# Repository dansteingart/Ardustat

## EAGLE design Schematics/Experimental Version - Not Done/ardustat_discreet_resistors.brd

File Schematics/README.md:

## What's in this folder:

### Working Version
This works

### Experimental Versions
Largely Don't work and are poorly documented.

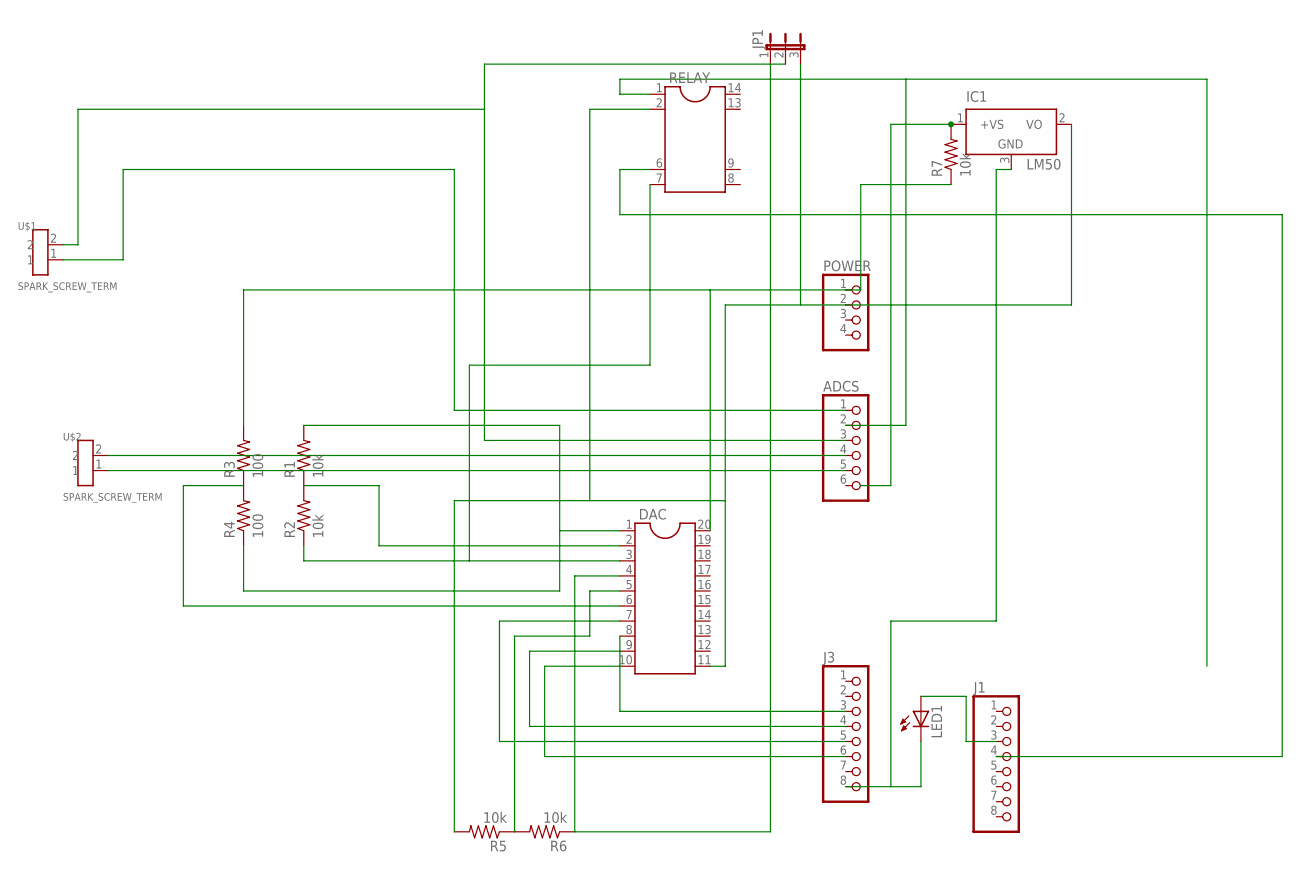
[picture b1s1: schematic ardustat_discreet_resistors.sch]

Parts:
ADCS: PINHD-1X6; 1X06
DAC: DIL20S; SOCKED-20
IC1: LM50; SOT23
J1, J3: PINHD-1X8; 1X08
JP1: JP2E; JP2
LED1: LED5MM
POWER: PINHD-1X4; 1X04
R1, R2, R5, R6, R7: 10k; 0207/12
R3, R4: 100; 0207/12
RELAY: DIL14/8
U$1, U$2: SPARK_SCREW_TERM

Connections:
unnamed: DAC.6, R3.1, R4.2
unnamed: DAC.10, J3.6
unnamed: DAC.9, J3.4
unnamed: DAC.8, J3.3
unnamed: DAC.7, J3.5
unnamed: J1.4, RELAY.6
unnamed: DAC.2, R1.1, R2.2
unnamed: ADCS.1, U$1.1
unnamed: J1.3, LED1.A
unnamed: DAC.20, POWER.1, R3.2, R7.1
unnamed: ADCS.2, RELAY.1
unnamed: DAC.5, R5.1, R6.2
unnamed: ADCS.5, U$2.1
unnamed: DAC.3, R2.1, RELAY.7
unnamed: DAC.4, JP1.1, R6.1
unnamed: IC1.3 (GND), J3.8, LED1.K (C)
unnamed: IC1.1 (+VS), R7.2
unnamed: ADCS.3, JP1.2, U$1.2
unnamed: ADCS.4, U$2.2
unnamed: DAC.1, DAC.11, IC1.2 (VO), JP1.3, POWER.2, R1.2, R4.1, R5.2, RELAY.2

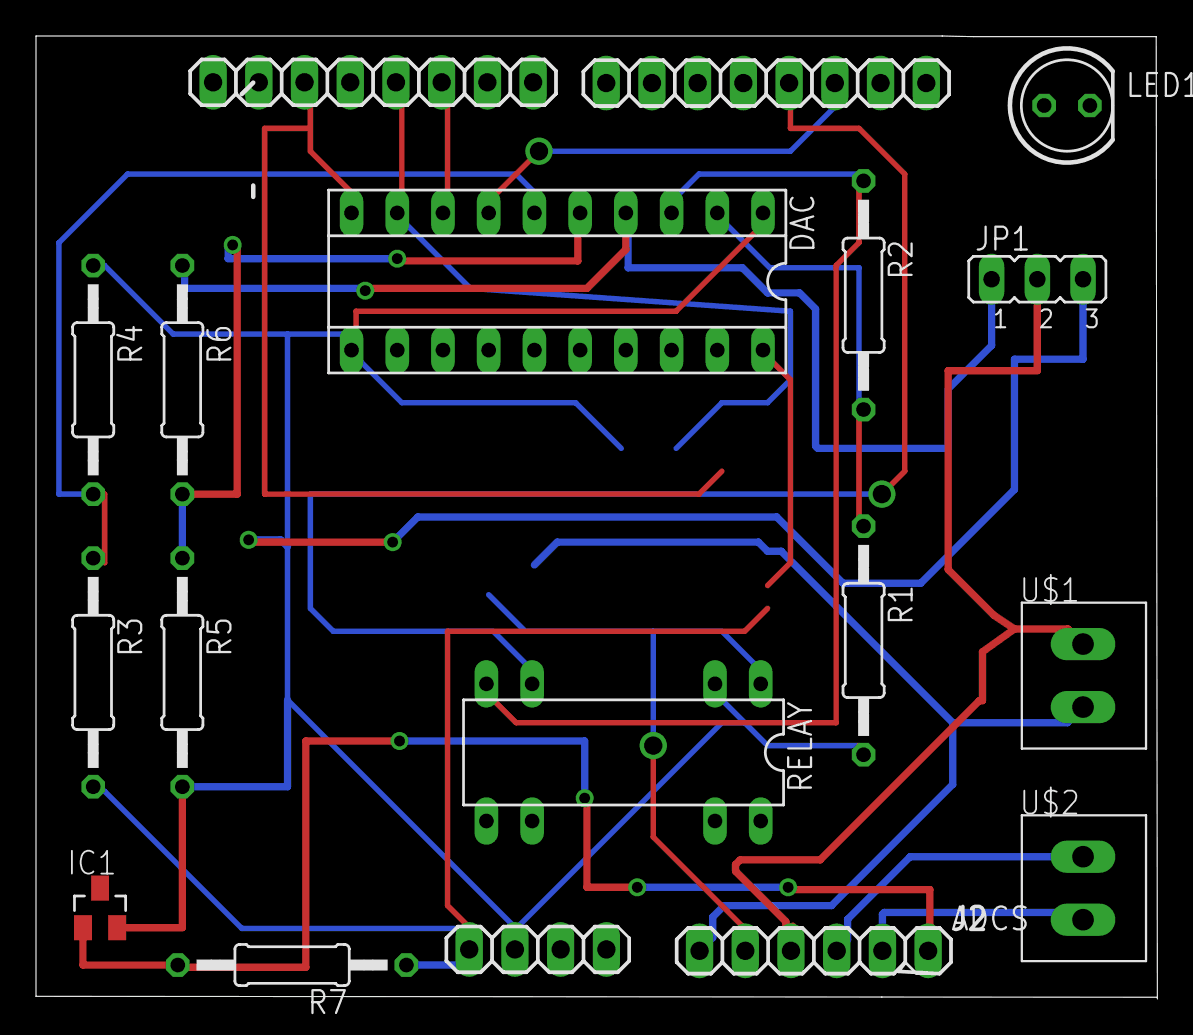
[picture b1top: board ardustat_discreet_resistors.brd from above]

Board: 2 copper layers, 62.3 x 53.5 mm, 18 parts (0 on the bottom side), 20 nets.

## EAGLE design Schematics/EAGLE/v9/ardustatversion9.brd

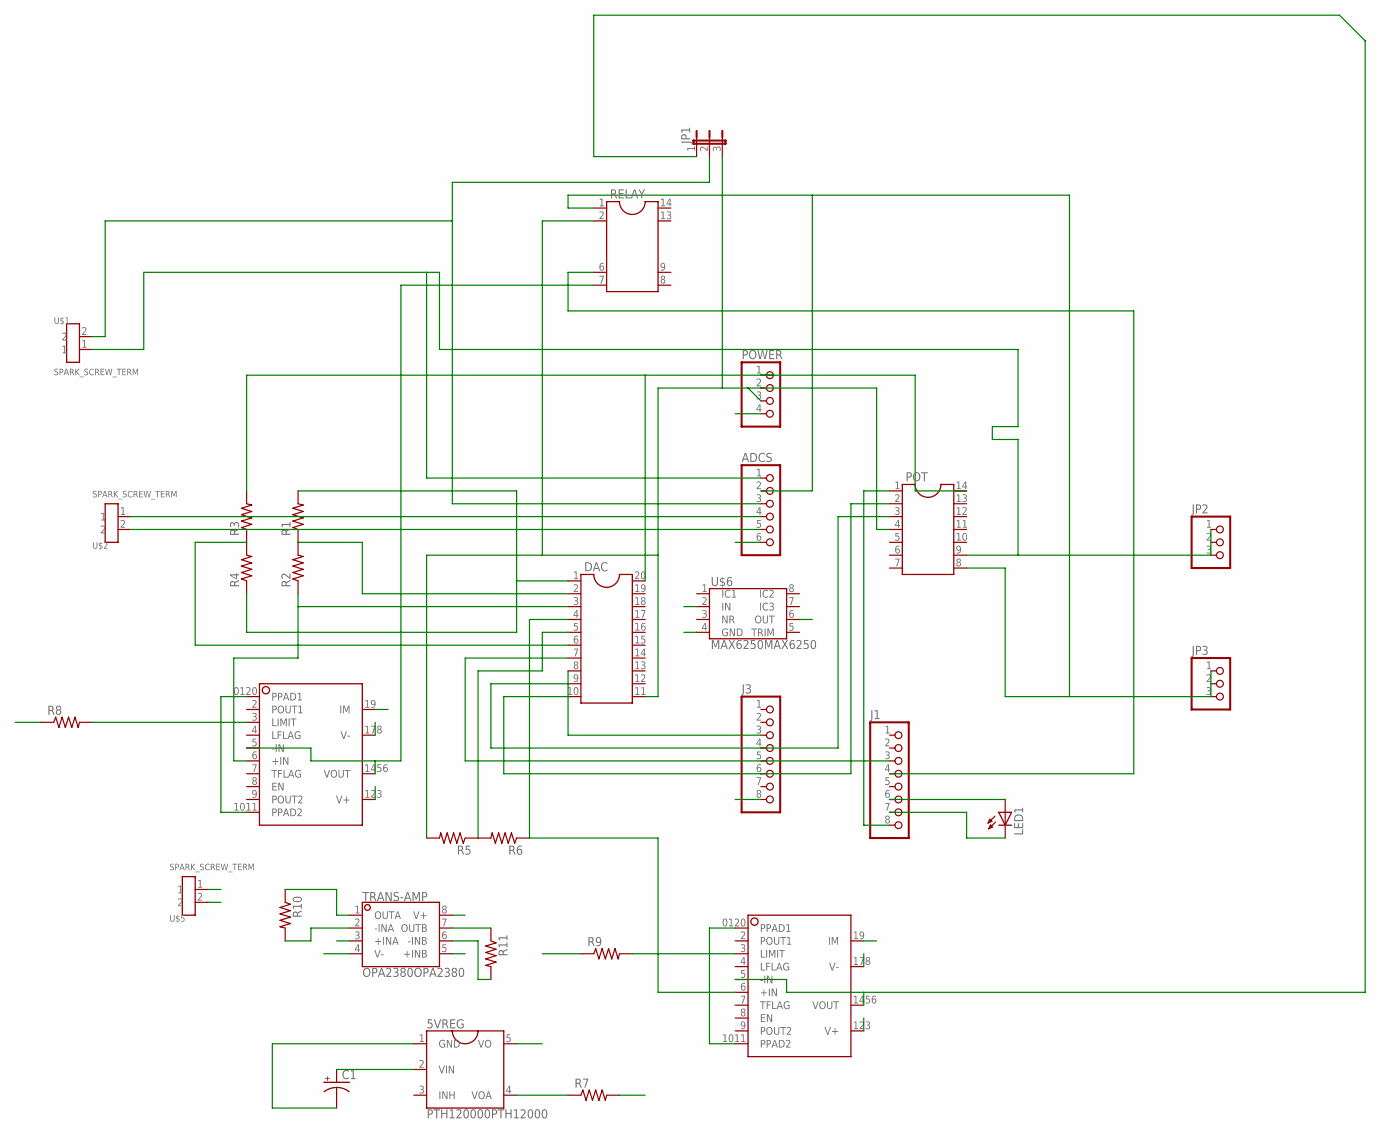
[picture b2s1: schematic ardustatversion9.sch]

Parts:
5VREG: PTH120000PTH12000; PTH120000
ADCS: PINHD-1X6; 1X06
C1: CPOL-USE5-10.5; E5-10,5
DAC: DIL20S; SOCKED-20
J1, J3: PINHD-1X8; 1X08
JP1: JP2E; JP2
JP2, JP3: PINHD-1X3; 1X03
LED1: LED5MM
POT: DIL14S; SOCKET-14
POWER: PINHD-1X4; 1X04
R1, R2, R3, R4, R5, R6, R8: R-US_R1206; R1206
R7, R9, R10, R11: R-US_M1206; M1206
RELAY: DIL14/8
TRANS-AMP: OPA2380OPA2380; OPA2380
U$1, U$2, U$5: SPARK_SCREW_TERM
U$3, U$4: OPA569OPA569; OPA569
U$6: MAX6250MAX6250; MAX6250

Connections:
GND: 5VREG.1 (GND), C1.-, DAC.1, DAC.11, JP1.3, POT.4, POWER.2, POWER.3, R1.2, R4.1, R5.2, R7.2, R8.1, R9.1, RELAY.2, TRANS-AMP.4 (V-), U$3.0120 (PPAD1), U$3.178 (V-), U$3.1011 (PPAD2), U$4.0120 (PPAD1), U$4.178 (V-), U$4.1011 (PPAD2), U$5.2, U$6.4 (GND)
unnamed: DAC.6, R3.1, R4.2
unnamed: DAC.10, J3.6, POT.2
unnamed: DAC.9, J3.4, POT.3
unnamed: DAC.8, J3.3
unnamed: DAC.7, J1.3
unnamed: J1.4, RELAY.6
unnamed: DAC.2, R1.1, R2.2
unnamed: ADCS.1, JP2.1, JP2.2, JP2.3, POT.9, U$1.1
unnamed: J1.8, POT.1
unnamed: R10.2, TRANS-AMP.2 (-INA), U$3.19 (IM)
unnamed: ADCS.2, JP3.1, JP3.2, JP3.3, POT.8, RELAY.1, TRANS-AMP.5 (+INB)
unnamed: DAC.5, R5.1, R6.2
unnamed: R8.2, U$3.3 (LIMIT)
unnamed: ADCS.5, R10.1, TRANS-AMP.1 (OUTA), U$2.2
unnamed: DAC.3, R2.1, U$3.6 (+IN)
unnamed: R9.2, U$4.3 (LIMIT)
unnamed: J1.6, LED1.A
unnamed: J1.7, LED1.K (C)
unnamed: 5VREG.5 (VO), TRANS-AMP.8 (V+), U$3.123 (V+), U$4.123 (V+)
unnamed: ADCS.4, U$2.1
unnamed: ADCS.3, JP1.2, TRANS-AMP.3 (+INA), U$1.2
unnamed: 5VREG.2 (VIN), C1.+, POWER.4, U$5.1, U$6.2 (IN)
unnamed: J3.8, U$6.6 (OUT)
unnamed: 5VREG.4 (VOA), R7.1
unnamed: RELAY.7, U$3.5 (-IN), U$3.1456 (VOUT)
unnamed: JP1.1, U$4.5 (-IN), U$4.1456 (VOUT)
unnamed: DAC.20, POT.14, POWER.1, R3.2
unnamed: DAC.4, R6.1, U$4.6 (+IN)
unnamed: ADCS.6, R11.1, TRANS-AMP.7 (OUTB)
unnamed: R11.2, TRANS-AMP.6 (-INB), U$4.19 (IM)

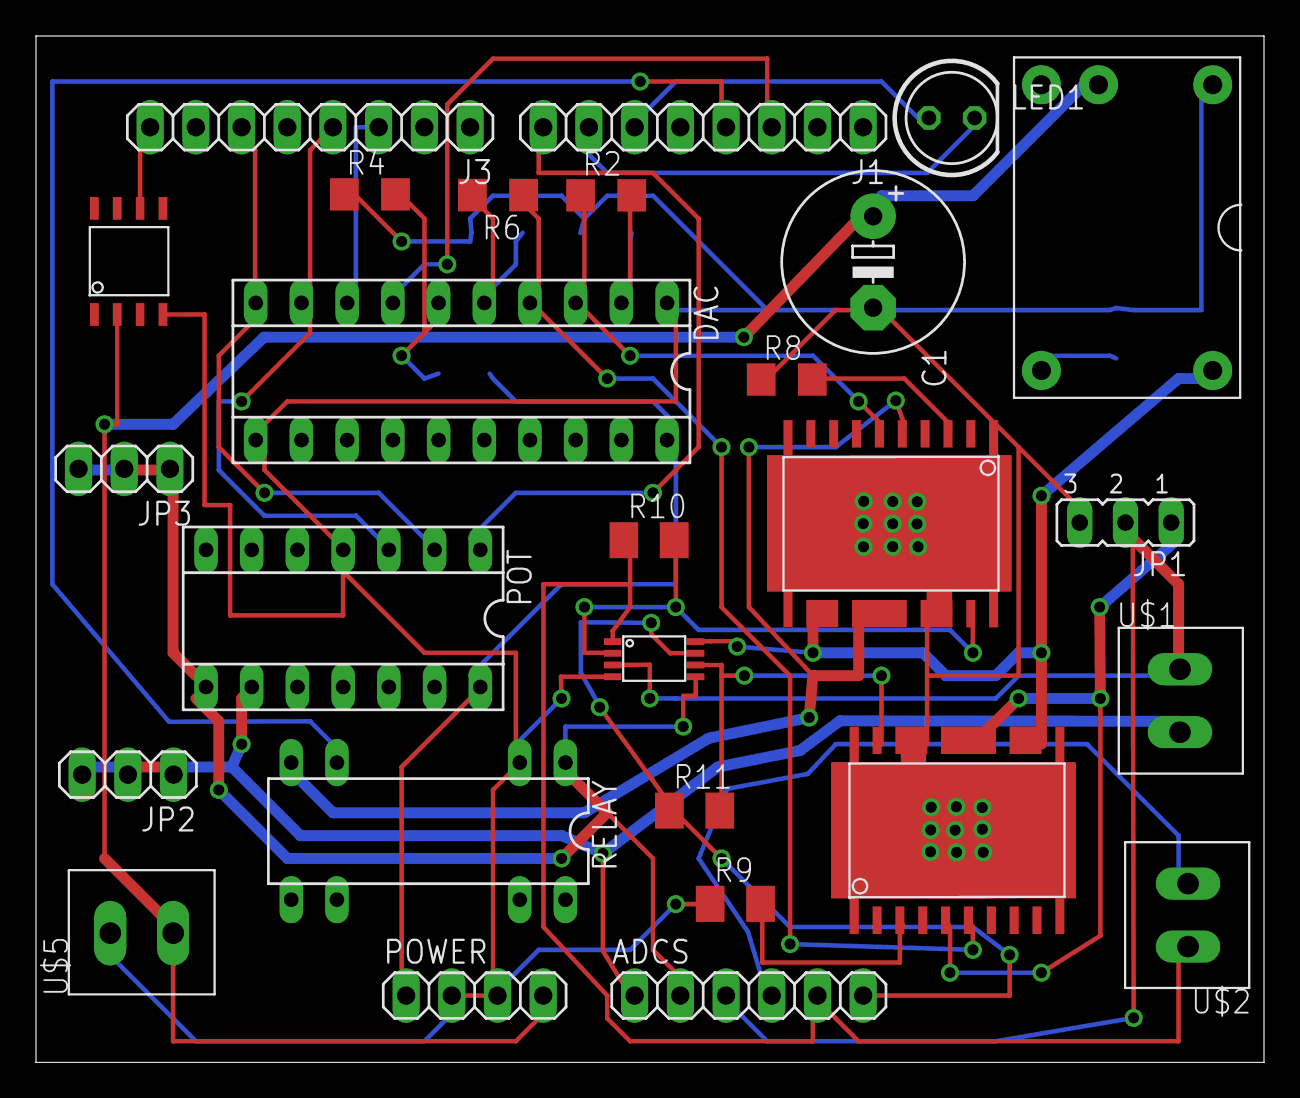
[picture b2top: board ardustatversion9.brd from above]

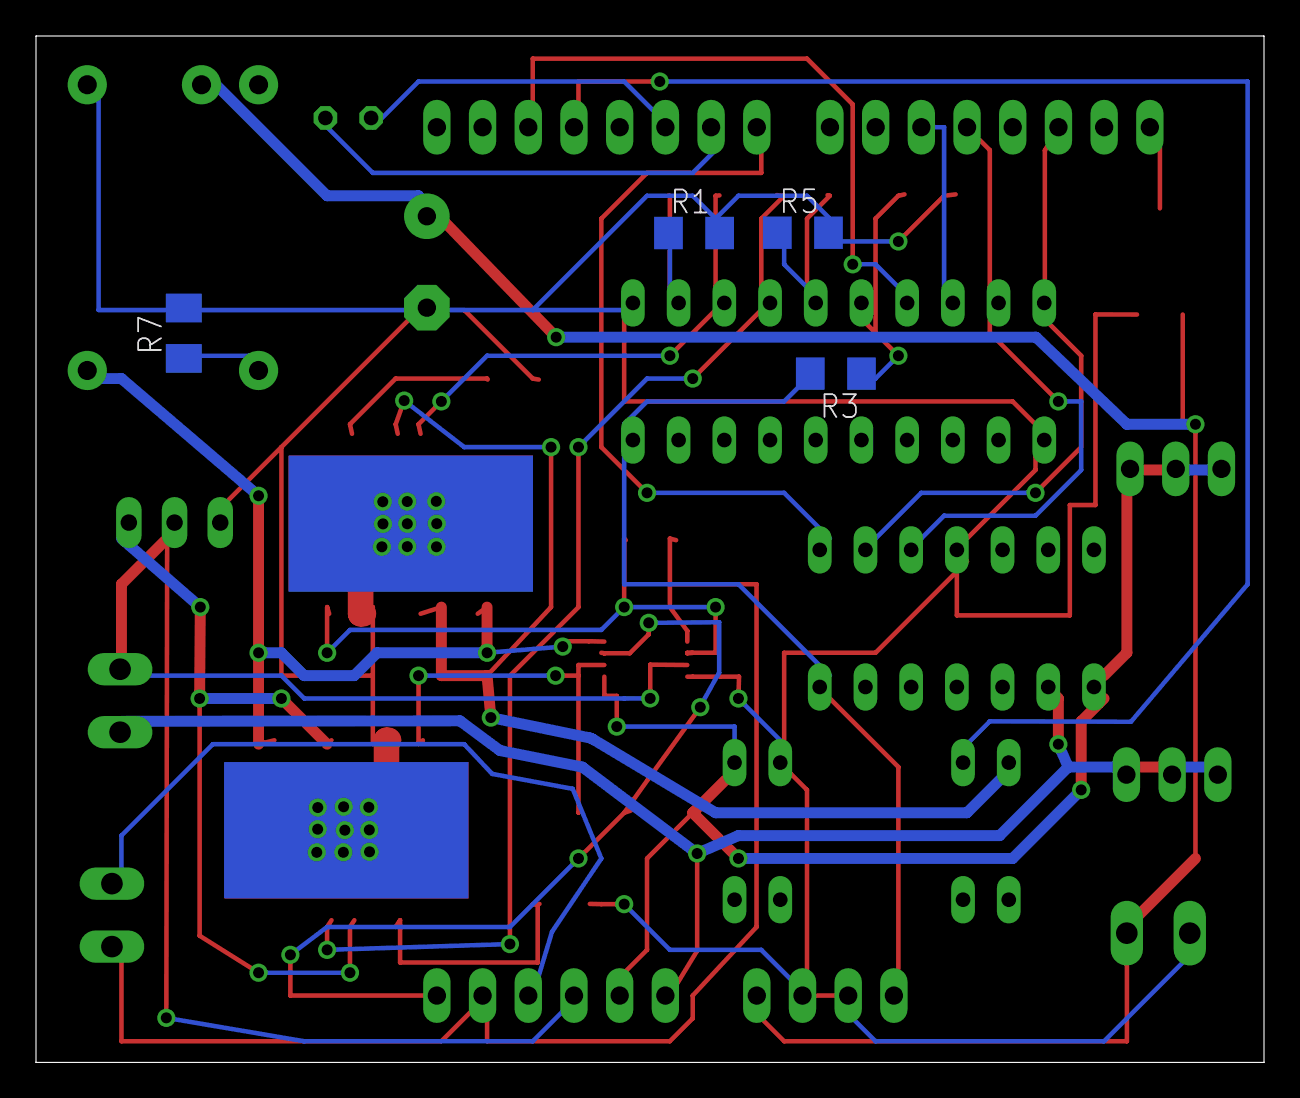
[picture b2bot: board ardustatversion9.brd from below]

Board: 2 copper layers, 68.2 x 57.0 mm, 31 parts (4 on the bottom side), 31 nets.

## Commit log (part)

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2011-07-11 First Commit
    Woo Hoo Github!
2011-07-11 Fixed Stupid Markdown Formatting Thing in readme
2011-07-11 again
2011-07-11 fixed all plot functions to work with correct libraries
2011-07-11 Linux additions/autoconnect
2011-07-11 cleaned plotting code
2011-07-11 Calibrate function; parsing
2011-07-12 fixes hither and thither
2011-07-12 a better potentiostat function (maybe) and some plot cleanup
2011-07-12 More updates
2011-07-12 more minor bugfixes
2011-07-12 Added alternative firmware
2011-07-12 Firmware modifications; graph tweaks
2011-07-12 Firmware
2011-07-13 New firmware cmd
2011-07-13 'X' fn auto-sets other dac to 0
2011-07-13 Fixed bug w/cell resistance calc & neg. voltage
2011-07-13 fixed setResistance() bug
2011-07-13 fixed another setResistance() bug
2011-07-13 setResistance() bug
2011-07-13 Bala's galvanostat mod
2011-07-13 Added rudimentary logging+plotting fn's
2011-07-14 More firmware cleanup
2011-07-14 Renamed v7 firmware
2011-07-14 made version 8 code, added a galvanostat test case
2011-07-14 Changed simplelog to logappend
2011-07-14 Fixed logappend bug
2011-07-14 misspelling
2011-07-14 nope
2011-07-14 Fixed firmware bug
2011-07-14 Added firmware bugfix to v8 code
2011-07-14 test scripts!
2011-07-18 Added same changes to v8 firmware
2011-07-18 Potentiostat function debugging
2011-07-18 More pstat improvements
2011-07-18 Fixed misspelling
2011-07-19 Started to work on web interface
2011-07-19 Added favicon
2011-07-19 Potentiostat fn in web interface
2011-07-19 Calibration in web interface
2011-07-19 Added EAGLE files
2011-07-19 Send raw command in web interface
2011-07-19 Added logging to web interface
2011-07-19 Updated logging program structure
2011-07-19 Added ardustatlogger.py file
2011-07-19 Added ask function
2011-07-19 Added ocv, shutdown to web interface
2011-07-20 Made web interface more robust
2011-07-20 Added cycling parsing
2011-07-20 Removed unneccesary 'raise' and 'print's
2011-07-20 Fixed 'situation 2'-- see issue 4
2011-07-20 Fixed logging issue
2011-07-20 Minor fixes
2011-07-20 Graph updates every 5 seconds
2011-07-21 Fixed socketwrite issues
2011-07-21 CSV files show up in dropdown
2011-07-21 Improved data table fn
2011-07-21 Minor bug
2011-07-25 Added conversion from .jsondata to .csv
2011-07-25 'cell voltage - reference electrode term' - bala's suggestion
2011-07-26 Removed misleading html text
2011-07-26 Made ardustat use a config file
2011-07-26 Fixed error in logging function for appending to existing log
2011-07-26 Fixed bullet points in readme
2011-07-26 Added 'setting' term
2011-07-26 Added bsd license
2011-07-27 Added time since beginning to log
2011-07-27 Fixed very bad bug in resbasis function
2011-07-27 Fixed enabledebugging
2011-07-27 New method of starting ardustat
2011-07-27 Verbose mode
2011-07-27 More plotting options
2011-07-30 Fixes and addition of a test script
    - added a "successful connect message" to OCV
    - removed a errant definit
    ion from firmware 7
2011-07-30 PID files in git folder: Read the PID.txt
2011-07-30 PID files in git folder
2011-07-31 startardustat doesn't need baudrate
2011-07-31 added old firmware JIC
2011-08-03 Edited readme.mdown via GitHub
2011-08-03 Moved PID related files to firmware directories
2011-08-04 Misplaced curvy bracket
2011-08-05 Ardustat V8 board descriptions
2011-08-05 Ardustat V7 descriptions
2011-08-05 big changes
    organized code
    improved sanity check
2011-08-06 Fixed Firmware
    Added Headers To Directories
    Fixed Head Import in PID.cpp
2011-08-07 Adding scripting functions
    CV, improved calibration, improved sanity check
2011-08-07 Added Functional CV and CV_Plot
2011-08-08 Fixed Galvanostat Bugs
    Fixed bugs in client code with respect to handling of negative currents
    Fixed bug in firmware_7_s with respect to handling potentials beyond the
    DAC limit
2011-08-08 Removed extra EAGLE directory
2011-08-08 added a v7 pinout schematic
2011-08-09 Socket read fail handling added to calibrate, galvanostat test
2011-08-12 connecting sanity check added
2011-08-13 Big changes all around
    - Added a move ground function to the library. Verified
    - Added a sanit
    y check for negative potentials
    - Changed the cv example to go negative
    - Firmware bug fixes (should never set potential out of range of DAC)
2011-08-13 Cleanups and Bug Fixes
    - Simple script to plot_cv over and over
    - Cleanups to Firmware_7_S
    - Cl
    eanups to CV (allow negative potentials)
2011-08-14 Big Changes: READ
    - Firmware 7_s bases changes from reference potential for potentiostat.
    THIS MEANS THAT ADC 3 (ref_ADC) MUST BE TIED TO GROUND FOR PSTAT TO WOR
    K.
    - Modifications to library to handle three electrode basis.
    REME
    MBER: For 2-electrode case tie REF to GND
2011-08-15 bug fix
    fixed bug in sanity check that caused the socket to hang for ~30 seconds after the program finished
2011-08-15 started an autoconnect function
2011-08-16 Edited Firmware/firmware_7_s/firmware_7_s.pde via GitHub
2011-08-17 Three Electrode Working
    found bug I introduced in the parsing code (ardustat firmware working).
    Fixed the library. Next commit will merge this with the master.
2011-08-17 Basic Fixes
2011-08-17 Wrote autoconnect function in library. Seems to work.
2011-08-18 Edited Python_Client/sanitycheck.py via GitHub
2011-09-02 autoconnect fixes
2011-09-06 New Eagle schematics with op amps
2011-10-02 Revert "Fixed autoconnect routine"
    This reverts commit b776ac54f3b7bb0f821cd5793e158389c28e5e88.
2011-10-02 Added Galvanostat_with_connect
2011-10-08 fixed .gitignore
2011-10-09 fixed a "," bug
2011-10-09 fixes for connector, again
2011-10-15 Real-time Python GUI for Ardustat software
2011-10-15 more readme instructions
2011-10-25 Adding convenience files
2011-10-25 Updating README.txt with more explicit instructions
2011-11-02 Added fixed resistor setting
2011-11-10 Final version of Op-Amp board
2011-11-27 A bunch of important changes
    1) Added a line to write the id into EEPROM on the ardustat, stable
    against restart (for auto locating the calibration) 2) Added some code
    to begin to handle this 3) Added a directory for serial only. Slowly
    realizing that the socket methods are making the perfect the enemy of
    the good.
2012-01-09 Working Serial_Python_Client
    Python_Client is probably broken
2012-01-09 Added NodeJS Section
2012-01-10 big changes to the nodeJS stuff
2012-01-10 started calibration functions
2012-01-11 NodeJS: Calibrate and Debug. Firmware7s:MoveGroundSafer
    NodeJS:
    Calibration, reading from arduino EEPROM for ID (set for now with
    V+(four digit id) (e.g. "V0016" for ID 16)
    Debugging a bit cleaner.
    Firmware7s:
    Set OCV = true when moving gnd
2012-01-11 Added Potentiostat and Galvanostat Functions
2012-01-11 refixed firmware
2012-01-13 placeholder for data director
2012-01-16 Stability Improvements to Node Code
2012-01-16 Node Instructions!
2012-01-17 Clean Up
2012-01-18 Changes to Node Stuctures
    Moved existing control structure to NodeJS/Ardustat_Control - Works Same
    Added the beginnings of a viewing server at NodeJS/Ardustat_Viewer.
    Open with node view_server.js
2012-01-20 removed glob, pass serial port as a command line option
    e.g. node expresserver.js /dev/tty.usbserial-A7007cCI
2012-01-20 screw glob
2012-01-23 Added basic cycling structure
    Only time limits for now.
    Of the following format:
    {"mode":"potentiostat","value":0.1,"cutoff_mode":"time","cutoff_value":5
    000}
    {"mode":"galvanostat","value":0.3,"cutoff_mode":"time","cutoff_value":50
    00}
2012-01-23 Added cycling instructions to readme
    +##Now with basic cycling
    +
    +go to http://localhost:port/cycler
    +
    +enter the following format to cycle
    +
2012-01-23 Cycling Improvements
2012-01-24 Added potential limits for cycling
2012-01-24 firmware 10s super beta
    experimental aliasing support. needs to be triple checked.
2012-01-25 rough but functional viewer up
    from Ardustat_Viewer start node view_server.js
    go to localhost:8000
2012-01-25 robusted logging/viewing
2012-01-26 added basic very rough needs work support for saving cycling parameters
2012-01-26 hacks to improve galvanostatic cycling reliability
    what really needs to happen is a proper ardustat confirmation. way too
    tired to considered right now.
2012-01-27 Added external power and current measuring pins
2012-02-01 Easy way to set ocv during cylcing. Just start a galvanostat phase with value 0
2012-02-01 fixed the pin positions
2012-02-10 Few fixes for the convenience file
2012-02-10 abstracted sample rate in s000_sample_rate. If you think the server is slowing down, change this to 500 or 1000.
2012-02-24 New start script with more automation
2012-02-25 Adding command-line option for setting polling rate. If no polling rate is specified, 100 ms will be selected by default
2012-02-25 Changing start script to incorporate command-line option for setting polling rate.
2012-03-07 fixing percent error
2012-03-07 still fixing percent thing
2012-03-07 fixed percent thing!
2012-03-22 Removing mongod start; mongod should start automatically at startup
2012-03-22 Convenience file for updating from github
2012-04-04 Ardustat version layout and library
2012-04-04 Version 9 schematic and board
2012-04-16 V9 pdf print
2012-04-16 removed junk files from v9
2012-04-18 Optimized v9
2012-06-11 New current measuring system
2012-06-11 Changed firmware as well
2012-06-11 Removed one file
2012-06-13 Fixed firmware_10s
2012-06-14 Commit successful
2012-06-14 Added script for linux
2012-06-14 Replaced serialport with serialport2
2012-06-14 Misc. code cleanup/comments/etc
2012-06-14 Changed back direct debug commands to override the queuer
2012-06-14 Removing test file
2012-06-14 More minor code fixes
2012-06-15 Windows support
2012-06-15 Misc improvements
2012-06-15 Added bash script to detect arduinos
2012-06-15 Fixed misspelling & removed unnecessary lib
2012-06-15 Added node_modules to .gitignore and removed them
2012-06-18 Added deprecated code to new branch
2012-06-18 Added deprecated firmware
2012-06-18 Added deprecated schematics
2013-11-26 Firmware Cleanup
    Made what's what
2013-11-26 Schematic Cleanup and Clarifications
2013-11-26 Simple Stat Start!
2013-12-08 Movement and ReadMe Chanbe
2013-12-08 Clarification of parts list
2014-09-10 Updated Firmware a Little
2014-09-10 Added Newest Firmware
2014-09-11 adding forwarder
2014-09-11 forwarder uploaded
2014-09-13 improving resistance algorithim
2014-09-18 took it off debug mode
2014-09-18 restructured, added experimental stuff
2014-09-18 more averaging play
2014-09-19 running average
2014-09-23 playing more with averaging stuff
2014-09-23 this stuff needs to be fixed
2014-10-13 playing around with resistance function from nz
2014-10-16 fixed watchdog thingy in simple one
2014-10-22 might work
2014-10-23 added new forwarder but its a little buggy
2014-11-05 temporary hack in firmware to keep track of what cycle
2014-11-18 added some stuff
2014-11-19 node controller/viewer in progress
2014-12-16 added some more stuff
2014-12-20 some rearranging
2015-01-16 playing with node client
2015-01-26 restructuring app a little
2015-01-27 added some socket stuff
2015-01-28 fixed bugs and updated cv
2015-02-03 added calibration and had a little tidy up"
2015-02-16 added package.json
2015-03-18 'irrelevant'
2015-03-18 hacky merge with ardustat_fancy_3
2015-03-19 cleaned up a little
2015-03-19 added better timing stuff
2015-03-19 added easy starting
2015-03-20 made plotting more efficient
2015-03-20 set up for pi
2015-03-20 fixed cv
2015-03-20 setup for rpi
2015-03-22 made some things nicer, auto port finding, debugged some plotting
2015-03-23 made things better
2015-03-24 found and removed a cv bug
2015-03-24 some port stuff
2015-03-27 updated analysis page a little, changed _clean.csv
2015-03-27 added some manual file viewing
2015-04-01 updated some stuff
2015-04-01 couple bugs removed
2015-04-06 fixed bug with ch1 plotting / saving etc
2015-04-06 fixed analysis bugs
2015-04-28 fixed some cv setting errors
2015-04-29 fixed calibration stuff
2015-06-14 added averager to outvolt
2015-07-09 ready updates
2015-07-09 readme update
2016-02-12 killed the deprecated folder. long live the simple implementation.
2016-02-12 edits and improvements
2016-02-12 submodule remove
2016-02-14 better fallback for resistance map.
2016-02-14 better test file
2016-02-16 fixed sleep bug
